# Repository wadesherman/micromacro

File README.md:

# micromacro
An 8 key macro keyboard

## Parts List
* 1x Sparkfun Pro Micro 5v
* 1x Breakaway Headers
* 8x Cherry Key Switches
* 8x Diodes
* 8x Keycaps
* 1x Case

Sparkfun Wishlist: <http://sfe.io/w149906](http://sfe.io/w149906>

## Assembly
1. Collect all your parts
  ![img][img_1]
  ![img][img_2]
  ![img][img_3]
2. Bend all the diodes - its easier and neater to bend them before
  ![img][img_4]
3. Populate the board with all the diodes and then solder them in place - bending the legs out a little will hold the diodes in place until you have a chance to solder them.
  ![img][img_5]
4. Solder the headers to the Pro Micro - it is easiest to just solder one or two pins to hold things together loosely.
  ![img][img_6]
5. Solder the Pro Micro to the PCB - again, one or two pins
  ![img][img_7]
6. Install Pro Micro to PCH and finish soldering all the rest of the pins
  ![img][img_8]
  ![img][img_9]
7. (optional) If using a plate, install the key switches to the plate
  ![img][img_10]
  ![img][img_11]
8. Install the switches to the PCB and solder.
  ![img][img_12]
9. Install keycaps.
  ![img][img_13]
10. Install contraption into case. (STL file in /case)
11. Flash firmware to ProMicro. (Arduino sketch in /firmware)

[img_1]: https://github.com/wadesherman/micromacro/blob/master/img/1_keycaps.JPG "Keycaps"
[img_2]: https://github.com/wadesherman/micromacro/blob/master/img/2_boards.JPG "PCB"
[img_3]: https://github.com/wadesherman/micromacro/blob/master/img/3_components.JPG "Components"
[img_4]: https://github.com/wadesherman/micromacro/blob/master/img/4_bend_diodes.JPG "Bend Diodes"
[img_5]: https://github.com/wadesherman/micromacro/blob/master/img/5_populate_diodes.JPG "Populate Diodes"
[img_6]: https://github.com/wadesherman/micromacro/blob/master/img/6_arduino_headers.JPG "Pro Micro Headers"
[img_7]: https://github.com/wadesherman/micromacro/blob/master/img/7_install_arduino.JPG "Pro Micro Headers"
[img_8]: https://github.com/wadesherman/micromacro/blob/master/img/8_solder_arduino_a.JPG "Solder"
[img_9]: https://github.com/wadesherman/micromacro/blob/master/img/9_solder_arduino_b.JPG "Solder"
[img_10]: https://github.com/wadesherman/micromacro/blob/master/img/10_key_plate_a.JPG "Key Plate"
[img_11]: https://github.com/wadesherman/micromacro/blob/master/img/11_key_plate_b.JPG "Key Plate"
[img_12]: https://github.com/wadesherman/micromacro/blob/master/img/12_solder_keys.JPG "Solder Keys"
[img_13]: https://github.com/wadesherman/micromacro/blob/master/img/13_install_keycaps.JPG "Install Keycaps"

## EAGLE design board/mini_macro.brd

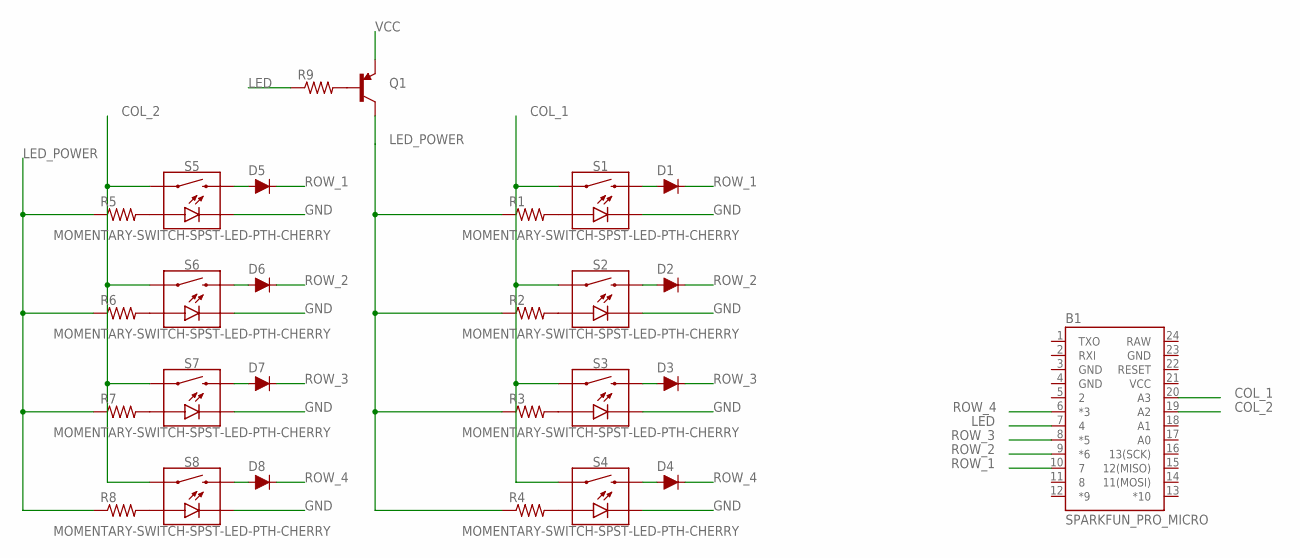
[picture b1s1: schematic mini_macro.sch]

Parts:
B1: SPARKFUN_PRO_MICRO
D1, D2, D3, D4, D5, D6, D7, D8: DIODE-1N4148
Q1: TRANSISTOR_PNPSMD; SOT23-3
R1, R2, R3, R4, R5, R6, R7, R8, R9: RESISTOR0603-RES; 0603-RES
S1, S2, S3, S4, S5, S6, S7, S8: MOMENTARY-SWITCH-SPST-LED-PTH-CHERRY; CHERRY-MX-LED

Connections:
COL_1: B1.20 (A3), S1.S1 (1), S2.S1 (1), S3.S1 (1), S4.S1 (1)
COL_2: B1.19 (A2), S5.S1 (1), S6.S1 (1), S7.S1 (1), S8.S1 (1)
GND: B1.3 (GND), B1.4 (GND), B1.23 (GND), S1.K (C), S2.K (C), S3.K (C), S4.K (C), S5.K (C), S6.K (C), S7.K (C), S8.K (C)
LED: B1.7 (4), R9.1
LED_POWER: Q1.3 (C), R1.1, R2.1, R3.1, R4.1, R5.1, R6.1, R7.1, R8.1
unnamed: D1.A, S1.S2 (2)
unnamed: D2.A, S2.S2 (2)
unnamed: D3.A, S3.S2 (2)
unnamed: D4.A, S4.S2 (2)
unnamed: D5.A, S5.S2 (2)
unnamed: D6.A, S6.S2 (2)
unnamed: D7.A, S7.S2 (2)
unnamed: D8.A, S8.S2 (2)
unnamed: R1.2, S1.A
unnamed: R2.2, S2.A
unnamed: R3.2, S3.A
unnamed: R4.2, S4.A
unnamed: R5.2, S5.A
unnamed: R6.2, S6.A
unnamed: R7.2, S7.A
unnamed: R8.2, S8.A
unnamed: Q1.1 (B), R9.2
RAW: B1.24 (RAW)
ROW_1: B1.10 (7), D1.C, D5.C
ROW_2: B1.9 (*6), D2.C, D6.C
ROW_3: B1.8 (*5), D3.C, D7.C
ROW_4: B1.6 (*3), D4.C, D8.C
VCC: B1.21 (VCC), Q1.2 (E)

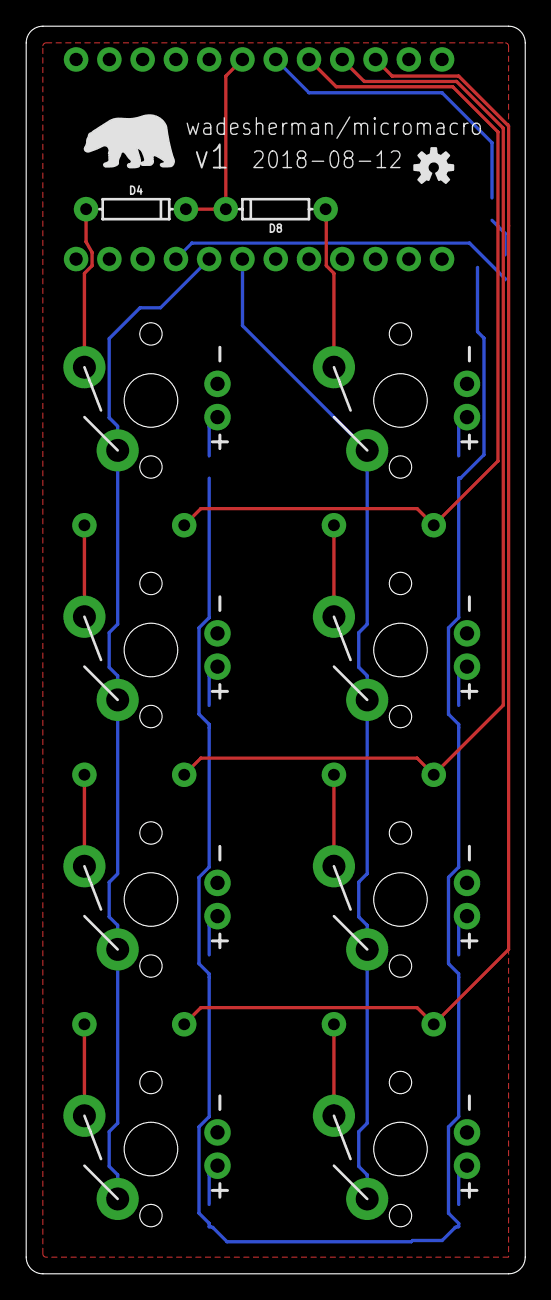
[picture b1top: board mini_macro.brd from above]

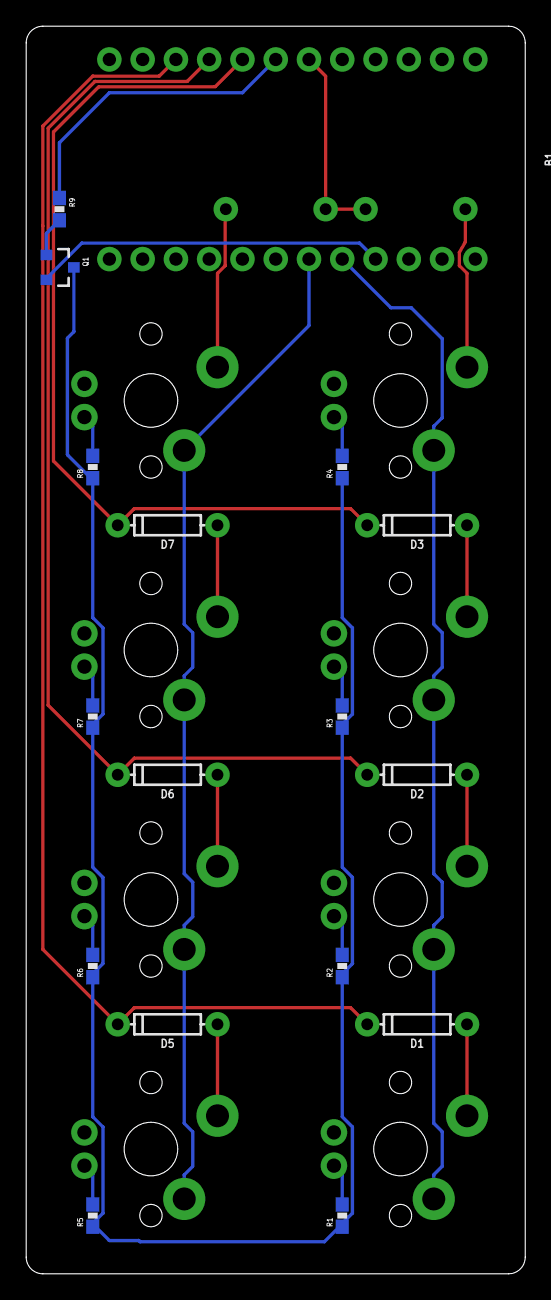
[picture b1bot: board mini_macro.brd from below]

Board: 2 copper layers, 38.1 x 95.2 mm, 29 parts (17 on the bottom side), 27 nets.

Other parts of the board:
U$1: OSHW-LOGO-S
U$2: BEAR

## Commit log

2018-09-04 Create File Structure (#1)
    * Create file structure
2018-09-06 initial commit with firmware, board files and case files
2019-01-03 add assembly images
2019-01-03 rename images

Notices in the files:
parts and their libraries:
SparkFun-Boards: Licensing: Creative Commons ShareAlike 4.0 International - https://creativecommons.org/licenses/by-sa/4.0
